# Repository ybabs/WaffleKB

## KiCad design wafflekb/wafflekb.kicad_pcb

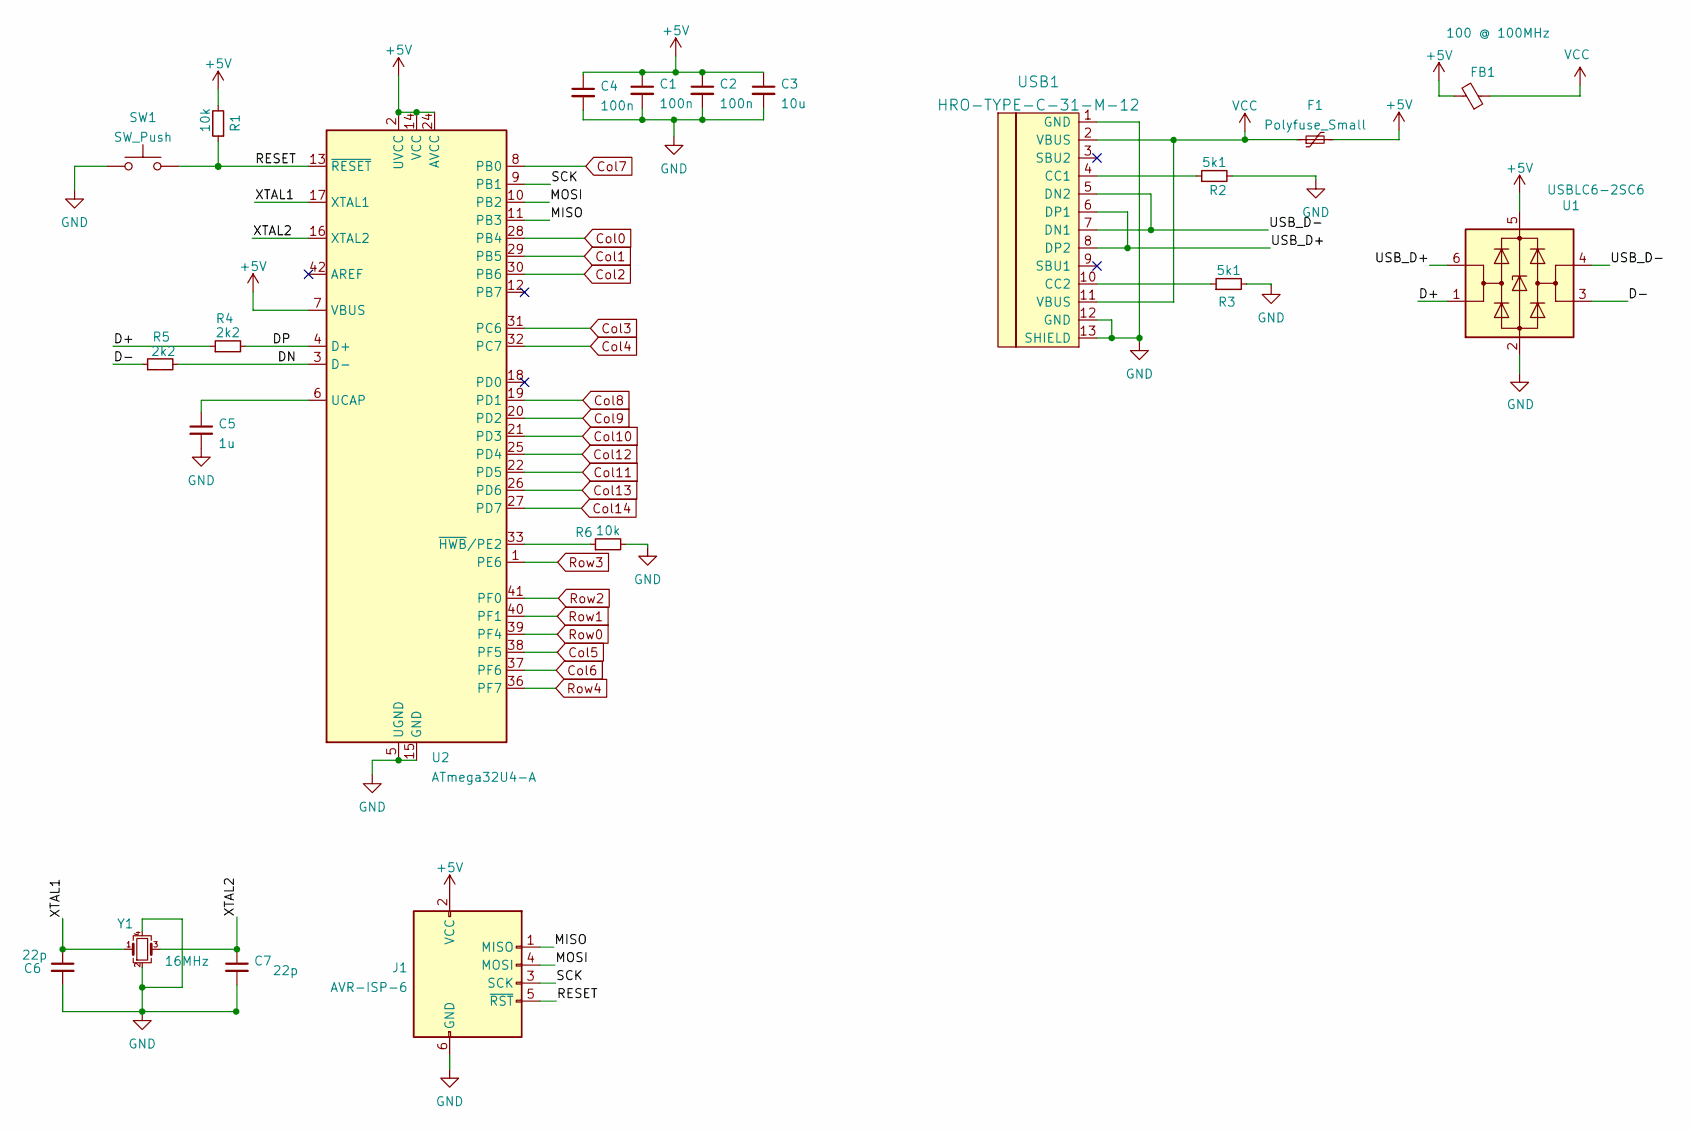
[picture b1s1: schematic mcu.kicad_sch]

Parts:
C1, C2, C4: 100n; C_0603_1608Metric
C3: 10u; C_0603_1608Metric
C5: 1u; C_0603_1608Metric
C6, C7: 22p; C_0603_1608Metric
F1: Polyfuse_Small; Fuse_1206_3216Metric
FB1: 100 @ 100MHz; L_0603_1608Metric; Manufacturer_Part_Number BLM21PG600SH1D
J1: AVR-ISP-6; Reset_Pretty-Mask
R1, R6: 10k; R_0603_1608Metric
R2, R3: 5k1; R_0603_1608Metric
R4, R5: 2k2; R_0603_1608Metric
SW1: SW_Push; SW_SPST_SKQG_WithStem
U1: USBLC6-2SC6; SOT-23-6; Manufacturer_Part_Number USBLC6-2SC6; LCSC Part # C7519
U2: ATmega32U4-A; TQFP-44_10x10mm_P0.8mm
USB1: HRO-TYPE-C-31-M-12
Y1: 16MHz; Crystal_SMD_3225-4Pin_3.2x2.5mm

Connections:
+5V: C1.1, C2.1, C3.1, C4.1, F1.2, FB1.2, J1.2 (VCC), R1.2, U1.5 (VBUS), U2.2 (UVCC), U2.7 (VBUS), U2.14 (VCC), U2.24 (AVCC), U2.34 (VCC), U2.44 (AVCC)
/microcontroller/D+: R4.1, U1.1 (I/O1)
/microcontroller/D-: R5.1, U1.3 (I/O2)
/microcontroller/DN: R5.2, U2.3 (D-)
/microcontroller/DP: R4.2, U2.4 (D+)
/microcontroller/MISO: J1.1 (MISO), U2.11 (PB3)
/microcontroller/MOSI: J1.4 (MOSI), U2.10 (PB2)
/microcontroller/RESET: J1.5 (~RST), R1.1, SW1.2, U2.13 (~RESET)
/microcontroller/SCK: J1.3 (SCK), U2.9 (PB1)
/microcontroller/USB_D+: U1.6 (I/O1), USB1.6 (DP1), USB1.8 (DP2)
/microcontroller/USB_D-: U1.4 (I/O2), USB1.5 (DN2), USB1.7 (DN1)
/microcontroller/XTAL1: C6.1, U2.17 (XTAL1), Y1.1
/microcontroller/XTAL2: C7.1, U2.16 (XTAL2), Y1.3
Col0: U2.28 (PB4); also elsewhere on the board
Col1: U2.29 (PB5); also elsewhere on the board
Col2: U2.30 (PB6); also elsewhere on the board
Col3: U2.31 (PC6); also elsewhere on the board
Col4: U2.32 (PC7); also elsewhere on the board
Col5: U2.38 (PF5); also elsewhere on the board
Col6: U2.37 (PF6); also elsewhere on the board
Col7: U2.8 (PB0); also elsewhere on the board
Col8: U2.19 (PD1); also elsewhere on the board
Col9: U2.20 (PD2); also elsewhere on the board
Col10: U2.21 (PD3); also elsewhere on the board
Col11: U2.22 (PD5); also elsewhere on the board
Col12: U2.25 (PD4); also elsewhere on the board
Col13: U2.26 (PD6); also elsewhere on the board
Col14: U2.27 (PD7); also elsewhere on the board
GND: C1.2, C2.2, C3.2, C4.2, C5.2, C6.2, C7.2, J1.6 (GND), R2.2, R3.2, R6.2, SW1.1, U1.2 (GND), U2.5 (UGND), U2.15 (GND), U2.23 (GND), U2.35 (GND), U2.43 (GND), USB1.1 (GND), USB1.12 (GND), USB1.13 (SHIELD), Y1.2, Y1.4
unnamed: C5.1, U2.6 (UCAP)
unnamed: R2.1, USB1.4 (CC1)
unnamed: R3.1, USB1.10 (CC2)
unnamed: R6.1, U2.33 (~HWB/PE2)
Row0: U2.39 (PF4); also elsewhere on the board
Row1: U2.40 (PF1); also elsewhere on the board
Row2: U2.41 (PF0); also elsewhere on the board
Row3: U2.1 (PE6); also elsewhere on the board
Row4: U2.36 (PF7); also elsewhere on the board
VCC: F1.1, FB1.1, USB1.2 (VBUS), USB1.11 (VBUS)

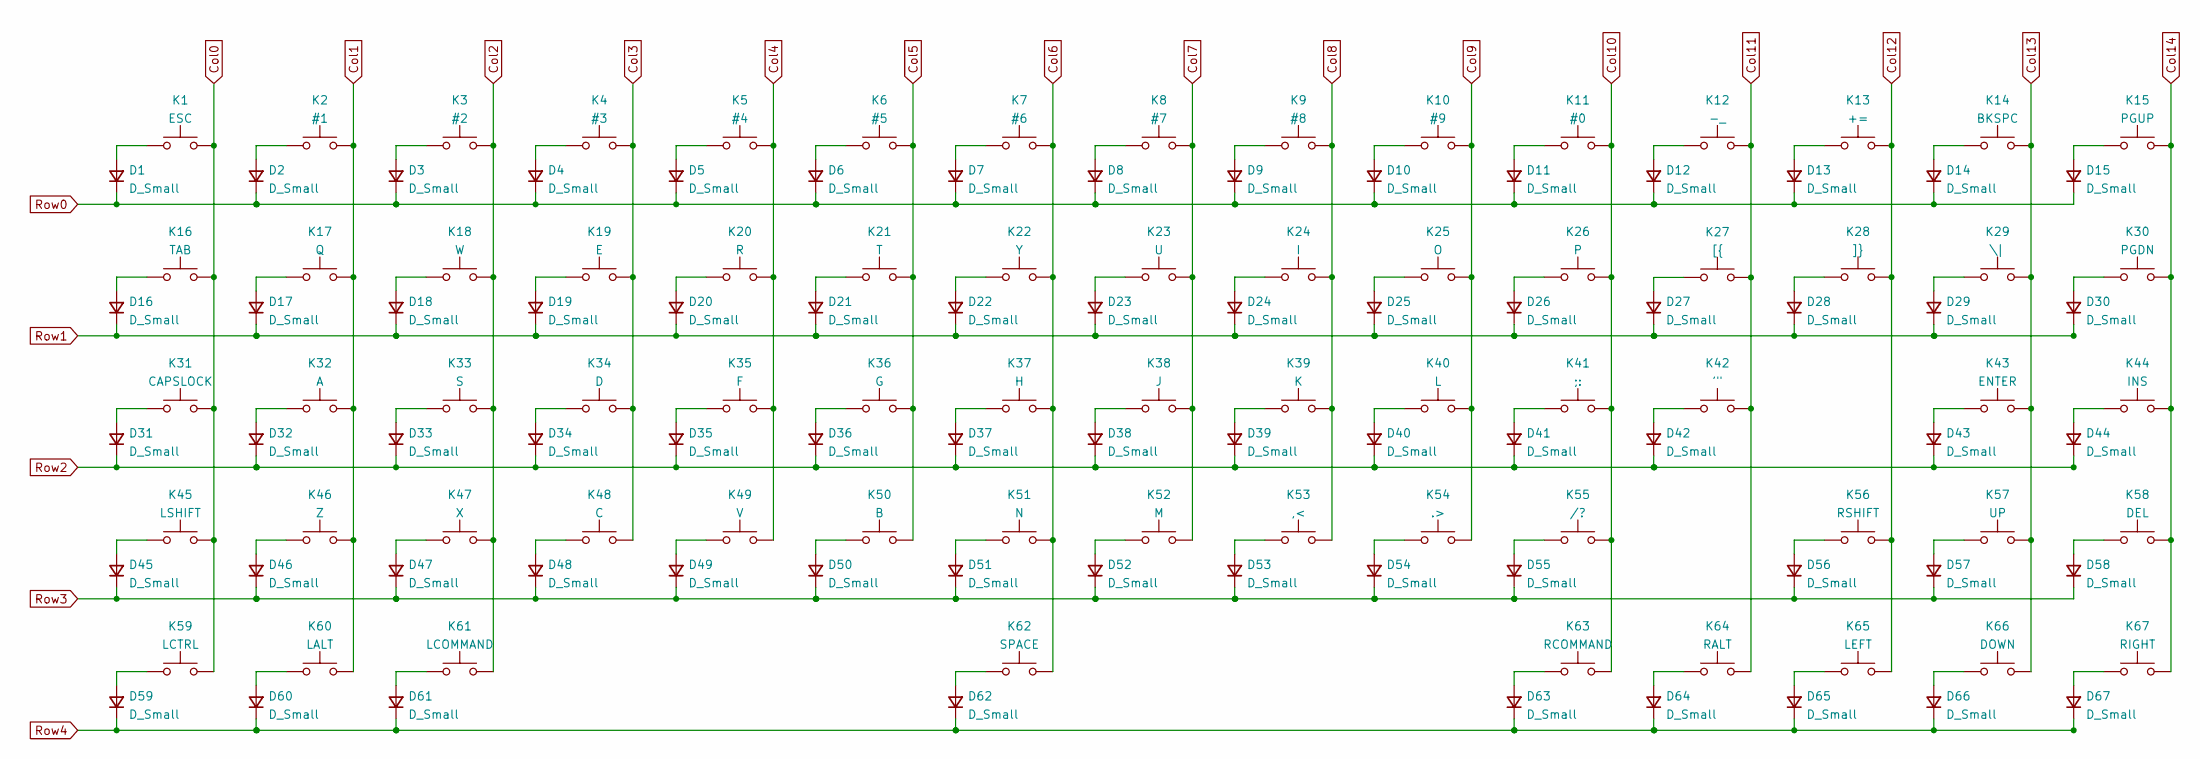
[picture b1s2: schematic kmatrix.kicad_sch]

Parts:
D1, D2, D3, D4, D5, D6, D7, D8, D9, D10, D11, D12, D13, D14, D15, D16, D17, D18, D19, D20, D21, D22, D23, D24, D25, D26, D27, D28, D29, D30, D31, D32, D33, D34, D35, D36, D37, D38, D39, D40, D41, D42, D43, D44, D45, D46, D47, D48, D49, D50, D51, D52, D53, D54, D55, D56, D57, D58, D59, D60, D61, D62, D63, D64, D65, D66, D67: D_Small; D_SOD-123
K1: ESC; ALPS-1U
K2: #1; ALPS-1U
K3: #2; ALPS-1U
K4: #3; ALPS-1U
K5: #4; ALPS-1U
K6: #5; ALPS-1U
K7: #6; ALPS-1U
K8: #7; ALPS-1U
K9: #8; ALPS-1U
K10: #9; ALPS-1U
K11: #0; ALPS-1U
K12: -_; ALPS-1U
K13: +=; ALPS-1U
K14: BKSPC; ALPS-2U
K15: PGUP; ALPS-1U
K16: TAB; ALPS-1.5U
K17: Q; ALPS-1U
K18: W; ALPS-1U
K19: E; ALPS-1U
K20: R; ALPS-1U
K21: T; ALPS-1U
K22: Y; ALPS-1U
K23: U; ALPS-1U
K24: I; ALPS-1U
K25: O; ALPS-1U
K26: P; ALPS-1U
K27: [{; ALPS-1U
K28: ]}; ALPS-1U
K29: \|; ALPS-1.5U
K30: PGDN; ALPS-1U
K31: CAPSLOCK; ALPS-1.75U
K32: A; ALPS-1U
K33: S; ALPS-1U
K34: D; ALPS-1U
K35: F; ALPS-1U
K36: G; ALPS-1U
K37: H; ALPS-1U
K38: J; ALPS-1U
K39: K; ALPS-1U
K40: L; ALPS-1U
K41: ;:; ALPS-1U
K42: '"; ALPS-1U
K43: ENTER; ALPS-2.25U
K44: INS; ALPS-1U
K45: LSHIFT; ALPS-2.25U
K46: Z; ALPS-1U
K47: X; ALPS-1U
K48: C; ALPS-1U
K49: V; ALPS-1U
K50: B; ALPS-1U
K51: N; ALPS-1U
K52: M; ALPS-1U
K53: ,<; ALPS-1U
K54: .>; ALPS-1U
K55: /?; ALPS-1U
K56: RSHIFT; ALPS-1.75U
K57: UP; ALPS-1U
K58: DEL; ALPS-1U
K59: LCTRL; ALPS-1.5U
K60: LALT; ALPS-1.25U
K61: LCOMMAND; ALPS-1.5U
K62: SPACE; ALPS-6.5U
K63: RCOMMAND; ALPS-1U
K64: RALT; ALPS-1.25U
K65: LEFT; ALPS-1U
K66: DOWN; ALPS-1U
K67: RIGHT; ALPS-1U

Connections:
Col0: K1.1, K16.1, K31.1, K45.1, K59.1; also elsewhere on the board
Col1: K2.1, K17.1, K32.1, K46.1, K60.1; also elsewhere on the board
Col2: K3.1, K18.1, K33.1, K47.1, K61.1; also elsewhere on the board
Col3: K4.1, K19.1, K34.1, K48.1; also elsewhere on the board
Col4: K5.1, K20.1, K35.1, K49.1; also elsewhere on the board
Col5: K6.1, K21.1, K36.1, K50.1; also elsewhere on the board
Col6: K7.1, K22.1, K37.1, K51.1, K62.1; also elsewhere on the board
Col7: K8.1, K23.1, K38.1, K52.1; also elsewhere on the board
Col8: K9.1, K24.1, K39.1, K53.1; also elsewhere on the board
Col9: K10.1, K25.1, K40.1, K54.1; also elsewhere on the board
Col10: K11.1, K26.1, K41.1, K55.1, K63.1; also elsewhere on the board
Col11: K12.1, K27.1, K42.1, K64.1; also elsewhere on the board
Col12: K13.1, K28.1, K56.1, K65.1; also elsewhere on the board
Col13: K14.1, K29.1, K43.1, K57.1, K66.1; also elsewhere on the board
Col14: K15.1, K30.1, K44.1, K58.1, K67.1; also elsewhere on the board
unnamed: D1.2 (A), K1.2
unnamed: D2.2 (A), K2.2
unnamed: D3.2 (A), K3.2
unnamed: D4.2 (A), K4.2
unnamed: D5.2 (A), K5.2
unnamed: D6.2 (A), K6.2
unnamed: D7.2 (A), K7.2
unnamed: D8.2 (A), K8.2
unnamed: D9.2 (A), K9.2
unnamed: D10.2 (A), K10.2
unnamed: D11.2 (A), K11.2
unnamed: D12.2 (A), K12.2
unnamed: D13.2 (A), K13.2
unnamed: D14.2 (A), K14.2
unnamed: D15.2 (A), K15.2
unnamed: D16.2 (A), K16.2
unnamed: D17.2 (A), K17.2
unnamed: D18.2 (A), K18.2
unnamed: D19.2 (A), K19.2
unnamed: D20.2 (A), K20.2
unnamed: D21.2 (A), K21.2
unnamed: D22.2 (A), K22.2
unnamed: D23.2 (A), K23.2
unnamed: D24.2 (A), K24.2
unnamed: D25.2 (A), K25.2
unnamed: D26.2 (A), K26.2
unnamed: D27.2 (A), K27.2
unnamed: D28.2 (A), K28.2
unnamed: D29.2 (A), K29.2
unnamed: D30.2 (A), K30.2
unnamed: D31.2 (A), K31.2
unnamed: D32.2 (A), K32.2
unnamed: D33.2 (A), K33.2
unnamed: D34.2 (A), K34.2
unnamed: D35.2 (A), K35.2
unnamed: D36.2 (A), K36.2
unnamed: D37.2 (A), K37.2
unnamed: D38.2 (A), K38.2
unnamed: D39.2 (A), K39.2
unnamed: D40.2 (A), K40.2
unnamed: D41.2 (A), K41.2
unnamed: D42.2 (A), K42.2
unnamed: D43.2 (A), K43.2
unnamed: D44.2 (A), K44.2
unnamed: D45.2 (A), K45.2
unnamed: D46.2 (A), K46.2
unnamed: D47.2 (A), K47.2
unnamed: D48.2 (A), K48.2
unnamed: D49.2 (A), K49.2
unnamed: D50.2 (A), K50.2
unnamed: D51.2 (A), K51.2
unnamed: D52.2 (A), K52.2
unnamed: D53.2 (A), K53.2
unnamed: D54.2 (A), K54.2
unnamed: D55.2 (A), K55.2
unnamed: D56.2 (A), K56.2
unnamed: D57.2 (A), K57.2
unnamed: D58.2 (A), K58.2
unnamed: D59.2 (A), K59.2
unnamed: D60.2 (A), K60.2
unnamed: D61.2 (A), K61.2
unnamed: D62.2 (A), K62.2
unnamed: D63.2 (A), K63.2
unnamed: D64.2 (A), K64.2
unnamed: D65.2 (A), K65.2
unnamed: D66.2 (A), K66.2
unnamed: D67.2 (A), K67.2
Row0: D1.1 (K), D2.1 (K), D3.1 (K), D4.1 (K), D5.1 (K), D6.1 (K), D7.1 (K), D8.1 (K), D9.1 (K), D10.1 (K), D11.1 (K), D12.1 (K), D13.1 (K), D14.1 (K), D15.1 (K); also elsewhere on the board
Row1: D16.1 (K), D17.1 (K), D18.1 (K), D19.1 (K), D20.1 (K), D21.1 (K), D22.1 (K), D23.1 (K), D24.1 (K), D25.1 (K), D26.1 (K), D27.1 (K), D28.1 (K), D29.1 (K), D30.1 (K); also elsewhere on the board
Row2: D31.1 (K), D32.1 (K), D33.1 (K), D34.1 (K), D35.1 (K), D36.1 (K), D37.1 (K), D38.1 (K), D39.1 (K), D40.1 (K), D41.1 (K), D42.1 (K), D43.1 (K), D44.1 (K); also elsewhere on the board
Row3: D45.1 (K), D46.1 (K), D47.1 (K), D48.1 (K), D49.1 (K), D50.1 (K), D51.1 (K), D52.1 (K), D53.1 (K), D54.1 (K), D55.1 (K), D56.1 (K), D57.1 (K), D58.1 (K); also elsewhere on the board
Row4: D59.1 (K), D60.1 (K), D61.1 (K), D62.1 (K), D63.1 (K), D64.1 (K), D65.1 (K), D66.1 (K), D67.1 (K); also elsewhere on the board

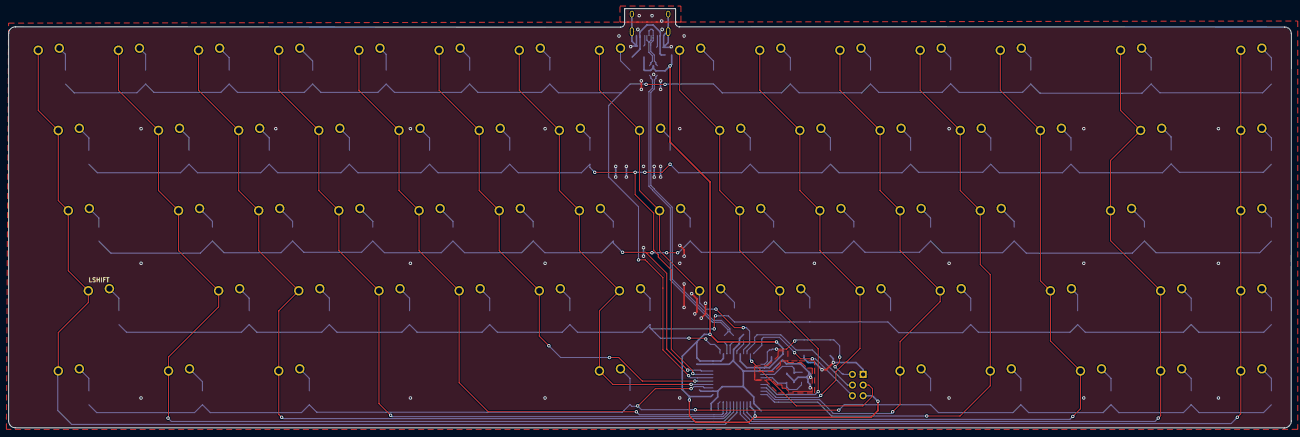
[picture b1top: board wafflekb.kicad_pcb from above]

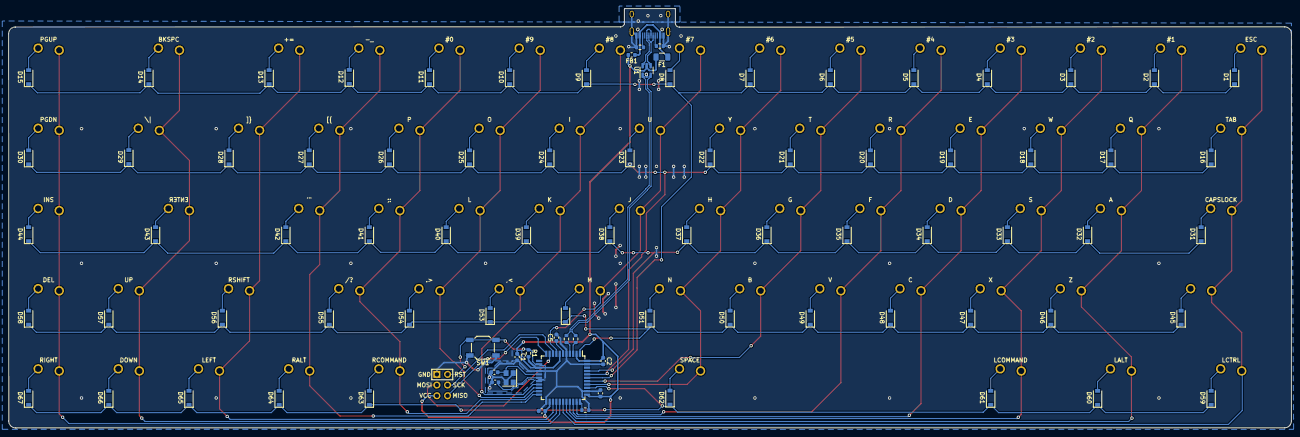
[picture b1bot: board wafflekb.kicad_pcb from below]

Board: 2 copper layers, 304.8 x 99.6 mm, 155 parts (88 on the bottom side), 106 nets.

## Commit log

2022-07-07 Add footprint libraries
2022-07-14 First Design
